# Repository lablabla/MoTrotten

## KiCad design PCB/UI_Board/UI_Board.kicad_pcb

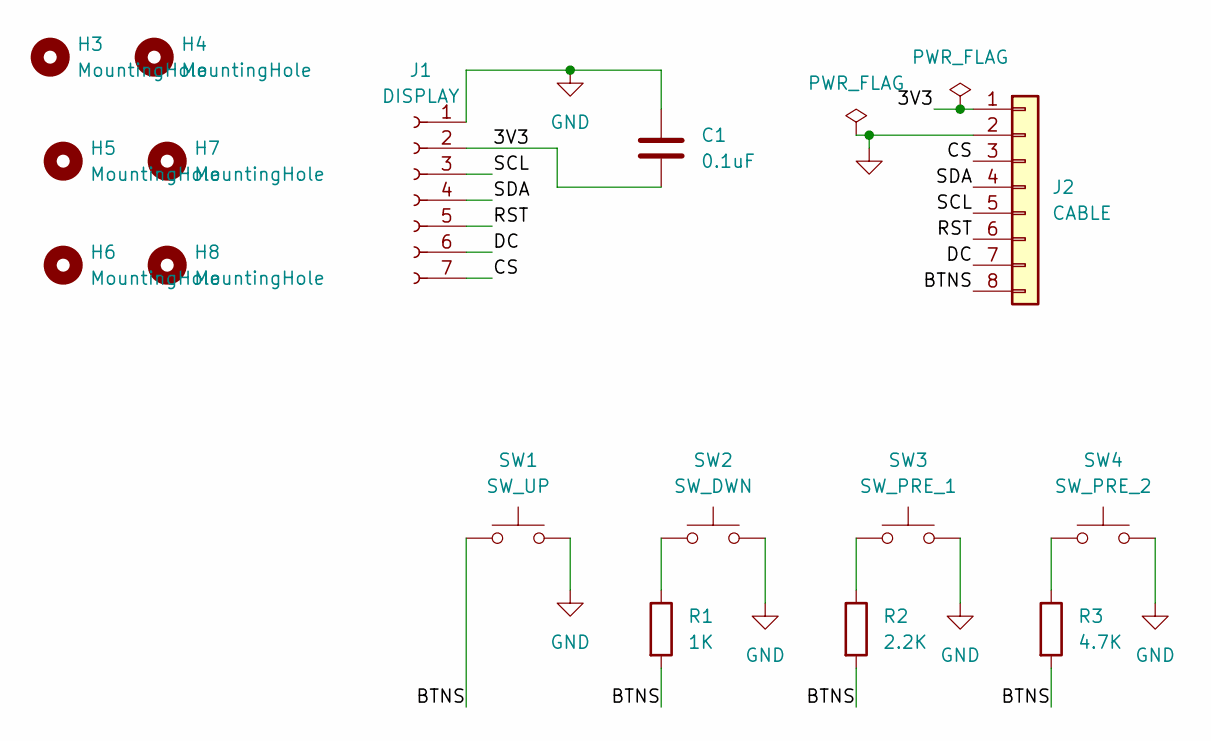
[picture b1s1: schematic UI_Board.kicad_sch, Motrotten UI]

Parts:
C1: 0.1uF; C_Rect_L7.2mm_W3.5mm_P5.00mm_FKS2_FKP2_MKS2_MKP2
H3, H4, H5, H6, H7, H8: MountingHole; MountingHole_3.2mm_M3
J1: DISPLAY; PinSocket_1x07_P2.54mm_Vertical
J2: CABLE; JST_XH_B8B-XH-A_1x08_P2.50mm_Vertical
R1: 1K; R_Axial_DIN0207_L6.3mm_D2.5mm_P7.62mm_Horizontal
R2: 2.2K; R_Axial_DIN0207_L6.3mm_D2.5mm_P7.62mm_Horizontal
R3: 4.7K; R_Axial_DIN0207_L6.3mm_D2.5mm_P7.62mm_Horizontal
SW1: SW_UP; SW_PUSH_6mm
SW2: SW_DWN; SW_PUSH_6mm
SW3: SW_PRE_1; SW_PUSH_6mm
SW4: SW_PRE_2; SW_PUSH_6mm

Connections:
/3V3: C1.2, J1.2, J2.1
/BTNS: J2.8, R1.2, R2.2, R3.2, SW1.1
/CS: J1.7, J2.3
/DC: J1.6, J2.7
/RST: J1.5, J2.6
/SCL: J1.3, J2.5
/SDA: J1.4, J2.4
GND: C1.1, J1.1, J2.2, SW1.2, SW2.2, SW3.2, SW4.2
unnamed: R1.1, SW2.1
unnamed: R2.1, SW3.1
unnamed: R3.1, SW4.1

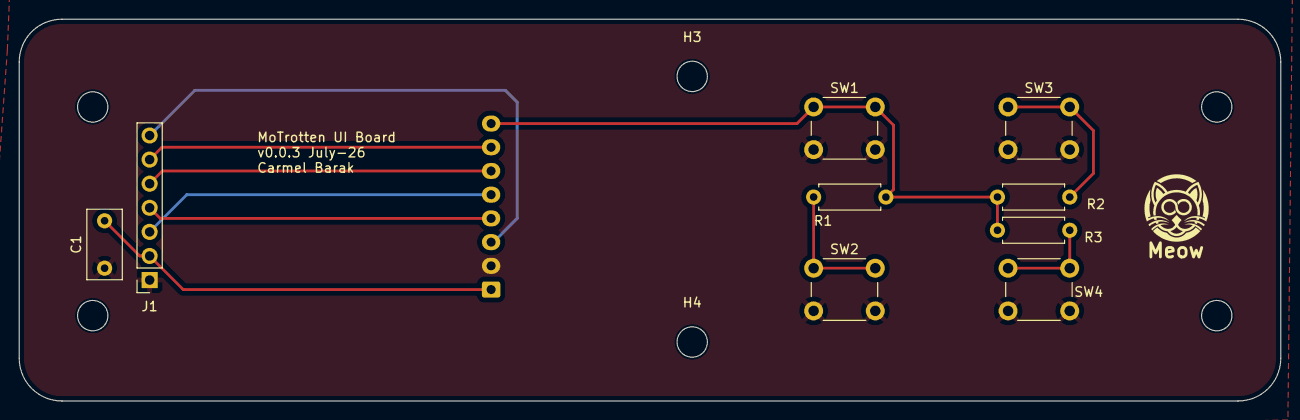
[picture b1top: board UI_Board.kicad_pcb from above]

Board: 2 copper layers, 133.0 x 40.2 mm, 16 parts (1 on the bottom side), 11 nets.

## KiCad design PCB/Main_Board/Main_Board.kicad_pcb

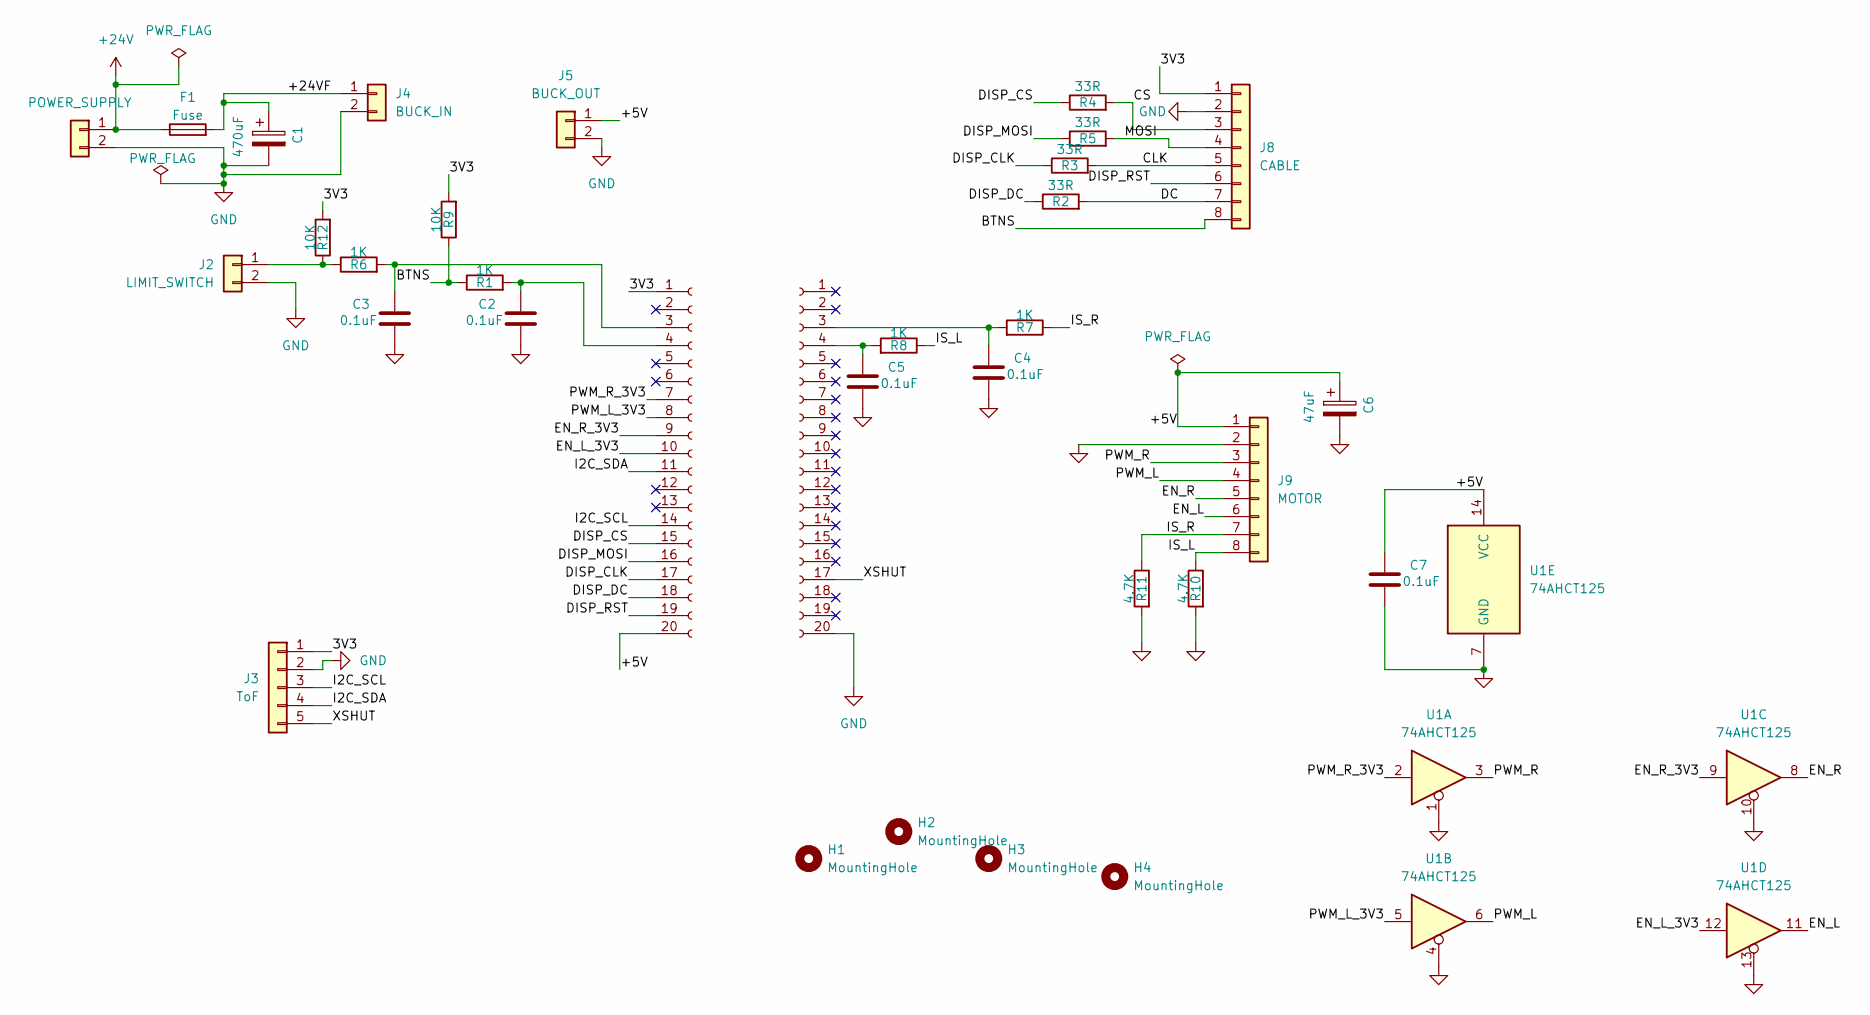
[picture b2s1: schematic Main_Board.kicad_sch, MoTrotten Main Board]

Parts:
C1: 470uF; CP_Radial_D10.0mm_P5.00mm
C2, C3, C4, C5, C7: 0.1uF; C_Rect_L7.2mm_W3.5mm_P5.00mm_FKS2_FKP2_MKS2_MKP2
C6: 47uF; CP_Radial_D10.0mm_P5.00mm
F1: Fuse; Fuseholder_Cylinder-5x20mm_Stelvio-Kontek_PTF78_Horizontal_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
H1, H2, H3, H4: MountingHole; MountingHole_3.2mm_M3
J1: POWER_SUPPLY; TerminalBlock_bornier-2_P5.08mm
J2: LIMIT_SWITCH; JST_PH_B2B-PH-K_1x02_P2.00mm_Vertical
J3: ToF; JST_PH_B5B-PH-K_1x05_P2.00mm_Vertical
J4: BUCK_IN; TerminalBlock_bornier-2_P5.08mm
J5: BUCK_OUT; TerminalBlock_bornier-2_P5.08mm
J6: ESP32_Left; PinSocket_1x20_P2.54mm_Vertical
J7: ESP32_Right; PinSocket_1x20_P2.54mm_Vertical
J8: CABLE; JST_XH_B8B-XH-A_1x08_P2.50mm_Vertical
J9: MOTOR; JST_XH_B8B-XH-A_1x08_P2.50mm_Vertical
R1, R6, R7, R8: 1K; R_Axial_DIN0207_L6.3mm_D2.5mm_P7.62mm_Horizontal
R2, R3, R4, R5: 33R; R_Axial_DIN0207_L6.3mm_D2.5mm_P7.62mm_Horizontal
R9, R12: 10K; R_Axial_DIN0207_L6.3mm_D2.5mm_P7.62mm_Horizontal
R10, R11: 4.7K; R_Axial_DIN0207_L6.3mm_D2.5mm_P7.62mm_Horizontal
U1: 74AHCT125; DIP-14_W7.62mm

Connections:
+24V: F1.1, J1.1
/3V3: J3.1, J6.1, J8.1, R9.2, R12.2; also elsewhere on the board
/+5V: C6.1, C7.1, J5.1, J6.20, J9.1, U1.14 (VCC)
/+24VF: C1.1, F1.2, J4.1
/BTNS: J8.8, R1.1, R9.1
/CLK: J8.5, R3.2
/CS: J8.3, R4.2
/DC: J8.7, R2.2
/DISP_CLK: J6.17, R3.1
/DISP_CS: J6.15, R4.1
/DISP_DC: J6.18, R2.1
/DISP_MOSI: J6.16, R5.1
/DISP_RST: J6.19, J8.6
/EN_L: J9.6, U1.11
/EN_L_3V3: J6.10, U1.12
/EN_R: J9.5, U1.8
/EN_R_3V3: J6.9, U1.9
/I2C_SCL: J3.3, J6.14; also elsewhere on the board
/I2C_SDA: J3.4, J6.11; also elsewhere on the board
/IS_L: J9.8, R8.1, R10.1
/IS_R: J9.7, R7.1, R11.1
/MOSI: J8.4, R5.2
/PWM_L: J9.4, U1.6
/PWM_L_3V3: J6.8, U1.5
/PWM_R: J9.3, U1.3
/PWM_R_3V3: J6.7, U1.2
/XSHUT: J3.5, J7.17
GND: C1.2, C2.2, C3.2, C4.2, C5.2, C6.2, C7.2, J1.2, J2.2, J3.2, J4.2, J5.2, J7.20, J8.2, J9.2, R10.2, R11.2, U1.1, U1.4, U1.7 (GND), U1.10, U1.13
unnamed: J2.1, R6.1, R12.1
unnamed: C3.1, J6.3, R6.2
unnamed: C2.1, J6.4, R1.2
unnamed: C4.1, J7.3, R7.2
unnamed: C5.1, J7.4, R8.2

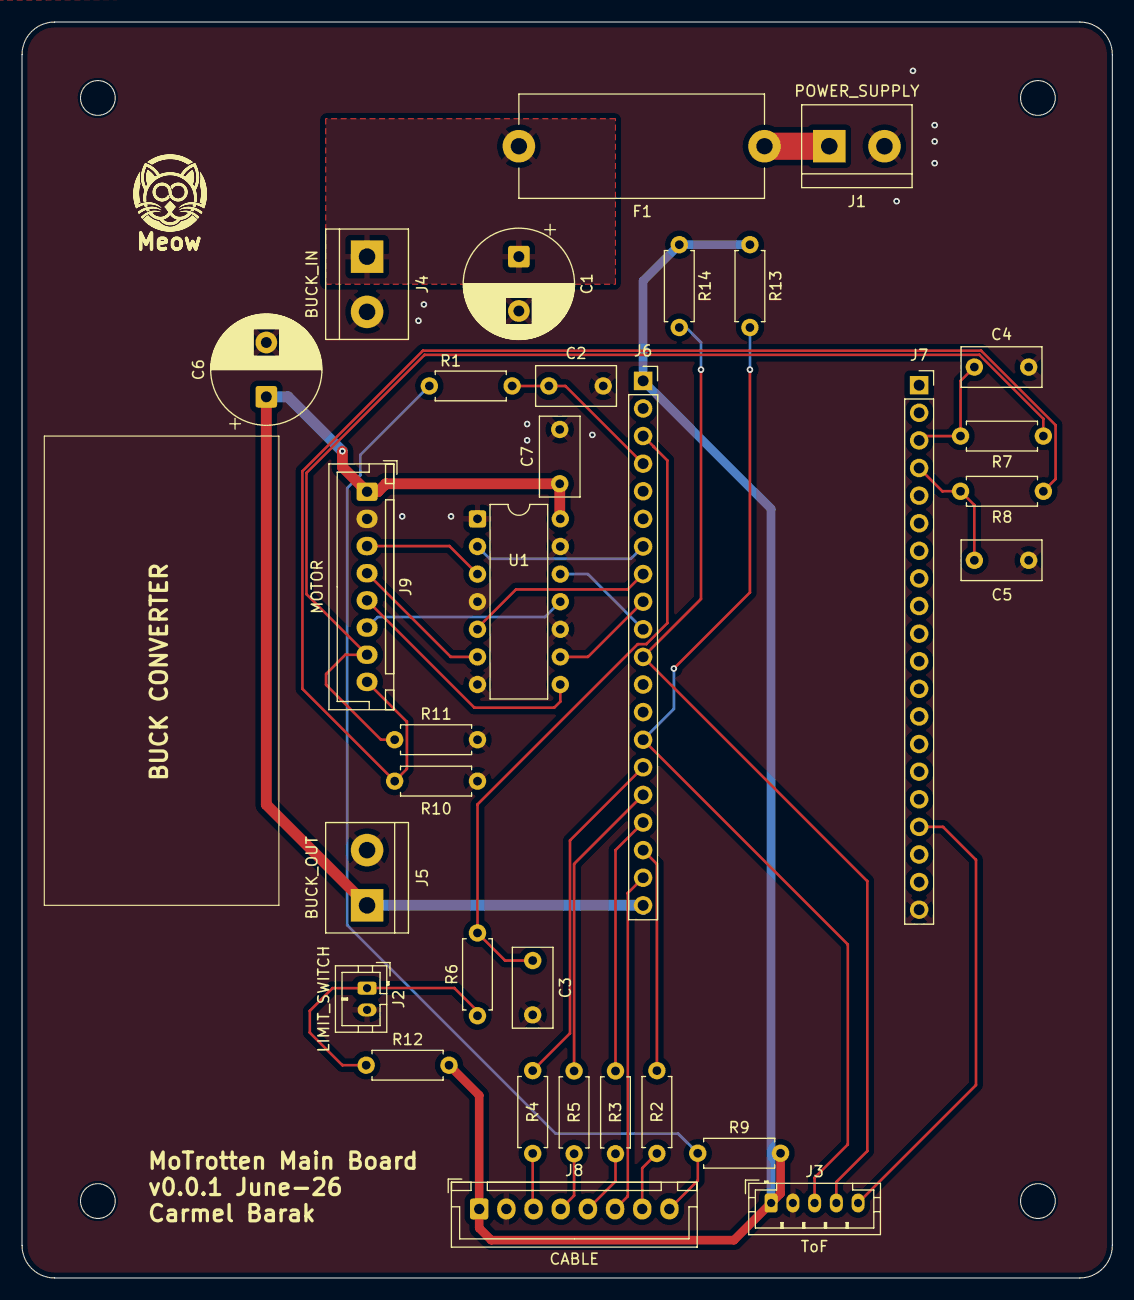
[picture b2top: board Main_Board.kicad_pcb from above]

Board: 2 copper layers, 100.3 x 115.6 mm, 36 parts (0 on the bottom side), 33 nets.

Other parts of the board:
R13, R14: 10K; R_Axial_DIN0207_L6.3mm_D2.5mm_P7.62mm_Horizontal

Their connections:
/3V3: R13.1, R14.1; also elsewhere on the board
/I2C_SCL: R13.2; also elsewhere on the board
/I2C_SDA: R14.2; also elsewhere on the board

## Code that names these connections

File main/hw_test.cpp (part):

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
static void test_pwm() {
    printf("\n=== TEST 2: PWM Output ===\n");
    printf("  Probe GPIO%d (PWM_R / UP) and GPIO%d (PWM_L / DOWN) with scope.\n",
           PIN_MOTOR_PWM_R, PIN_MOTOR_PWM_L);
    printf("  Expect %dHz, 10-bit PWM ramping 0%%→100%%→0%% on each channel.\n",
           MOTOR_LEDC_FREQ_HZ);
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
    for (int ch = 0; ch < 2; ch++) {
        ledc_channel_t channel = (ch == 0) ? MOTOR_LEDC_CH_R : MOTOR_LEDC_CH_L;
        const char* label = (ch == 0) ? "PWM_R (UP)" : "PWM_L (DOWN)";
        printf("  Ramping %s...\n", label);
        for (int duty = 0; duty <= MOTOR_MAX_DUTY; duty += 51) {
            ledc_set_duty(MOTOR_LEDC_MODE, channel, duty);
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static void test_vl53l0x() {
    printf("\n=== TEST 7: VL53L0X I2C ===\n");
    printf("  SDA=GPIO%d  SCL=GPIO%d  freq=%dkHz  addr=0x%02X\n",
           PIN_I2C_SDA, PIN_I2C_SCL, I2C_FREQ_HZ / 1000, VL53L0X_ADDR);

    i2c_master_bus_config_t bus_cfg = {
        .i2c_port          = I2C_PORT,
        .sda_io_num        = PIN_I2C_SDA,
        .scl_io_num        = PIN_I2C_SCL,
        .clk_source        = I2C_CLK_SRC_DEFAULT,
        .glitch_ignore_cnt = 7,
        .flags             = { .enable_internal_pullup = false },
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static void test_tof_range() {
    printf("\n=== TEST t: VL53L0X Range Readings ===\n");
    printf("  SDA=GPIO%d  SCL=GPIO%d  addr=0x%02X\n",
           PIN_I2C_SDA, PIN_I2C_SCL, VL53L0X_ADDR);

    i2c_master_bus_config_t bus_cfg = {
        .i2c_port          = I2C_PORT,
        .sda_io_num        = PIN_I2C_SDA,
        .scl_io_num        = PIN_I2C_SCL,
        .clk_source        = I2C_CLK_SRC_DEFAULT,
        .glitch_ignore_cnt = 7,
        .flags             = { .enable_internal_pullup = false },
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    if (s_panel) return true;

    spi_bus_config_t bus_cfg = {
        .mosi_io_num     = PIN_DISP_MOSI,
        .miso_io_num     = -1,
        .sclk_io_num     = PIN_DISP_CLK,
        .quadwp_io_num   = -1,
        .quadhd_io_num   = -1,
        .max_transfer_sz = DISP_WIDTH * sizeof(uint16_t),
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    if (r != ESP_OK) return false;

    esp_lcd_panel_io_spi_config_t io_cfg = {
        .cs_gpio_num          = PIN_DISP_CS,
        .dc_gpio_num          = PIN_DISP_DC,
        .spi_mode             = 0,
        .pclk_hz              = DISP_SPI_FREQ_HZ,
        .trans_queue_depth    = 4,
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    if (r != ESP_OK) return false;

    esp_lcd_panel_dev_config_t panel_cfg = {
        .reset_gpio_num = PIN_DISP_RST,
        .rgb_ele_order  = LCD_RGB_ELEMENT_ORDER_BGR,
        .bits_per_pixel = 16,
        .flags          = { .reset_active_high = 0 },
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static void test_display() {
    printf("\n=== TEST 9: Display (ST7789 %dx%d) ===\n", DISP_WIDTH, DISP_HEIGHT);
    printf("  MOSI=GPIO%d CLK=GPIO%d CS=GPIO%d DC=GPIO%d RST=GPIO%d\n",
           PIN_DISP_MOSI, PIN_DISP_CLK, PIN_DISP_CS, PIN_DISP_DC, PIN_DISP_RST);
    if (!display_ready(true)) return;

    // --- Solid colour fills ---
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
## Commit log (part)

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2025-12-12 Updated to use tasks + cleanups
2025-12-12 Add display management and motor control features
    - Implement DisplayManager class for handling display initialization and rendering.
    - Create MotorDriver class for motor control with soft start and stop functionality.
    - Update CMakeLists.txt to include new source files.
    - Modify desk_config.h to add display pin configurations.
    - Enhance main.cpp with GUI task and motor control logic.
    - Update dependencies in idf_component.yml and dependencies.lock.
2025-12-12 Add MIT License to the project
2025-12-12 Add UIManager class and integrate UI features
    - Introduced UIManager for managing UI elements and animations.
    - Updated display_manager to include new UI functionalities.
    - Modified main.cpp to utilize UIManager and manage UI states.
    - Adjusted CMakeLists.txt to include ui_manager.cpp.
    - Updated desk_config.h for display pin configuration.
    - Cleaned up commented code in main.cpp for better readability.
2025-12-13 Add startup animation to UIManager and improve GUI task initialization
2025-12-13 Refactor UIManager: Remove preset move functionality and adjust manual move logic
2025-12-13 Enhance sensor_task: Integrate I2C master bus and VL53L0X device initialization
2025-12-27 Add VL53L0X header file for time-of-flight distance sensor
2025-12-27 Refactor motor driver: Implement stall detection and improve I2C integration for VL53L0X sensor
2026-02-03 Initial PCB board commit. 1st revision of main board
2026-02-03 Minor fixes
2026-02-04 Added UI board Cosmetics in main board
2026-02-07 Cleanup main board + fixed GPIOs used
2026-02-09 Added fuse + cleanups
2026-02-21 Updated boards and added DRU files
2026-02-23 Updated boards
2026-03-29 Added decoupling capacitor to AHCT
2026-06-03 feat(display): update display width to 320 and add display diagnostic tests
2026-06-03 Add junctions and wires for improved connectivity on Main Board schematic
    - Introduced multiple junctions at specified coordinates to enhance circuit connections.
    - Updated wire connections to reflect new junction placements and ensure proper routing.
    - Adjusted component positions and labels for clarity and consistency.
    - Added two resistors (R13 and R14) with specified values and footprints to the schematic.
    - Updated GND symbol and its properties to align with new layout.
2026-06-12 Port full firmware rewrite from claude_impl: LEDC motor driver with stall detection, button/height/NVS managers, hw_test harness
    Replaces the legacy MCPWM-based main.cpp/motor_driver with app_main.cpp
    and the new module set (button_reader, height_sensor, nvs_manager) used
    by hw_test.cpp. Pin/PWM/current-sense config in desk_config.h now matches
    hw_test.cpp exactly. display_manager carried over unchanged.
